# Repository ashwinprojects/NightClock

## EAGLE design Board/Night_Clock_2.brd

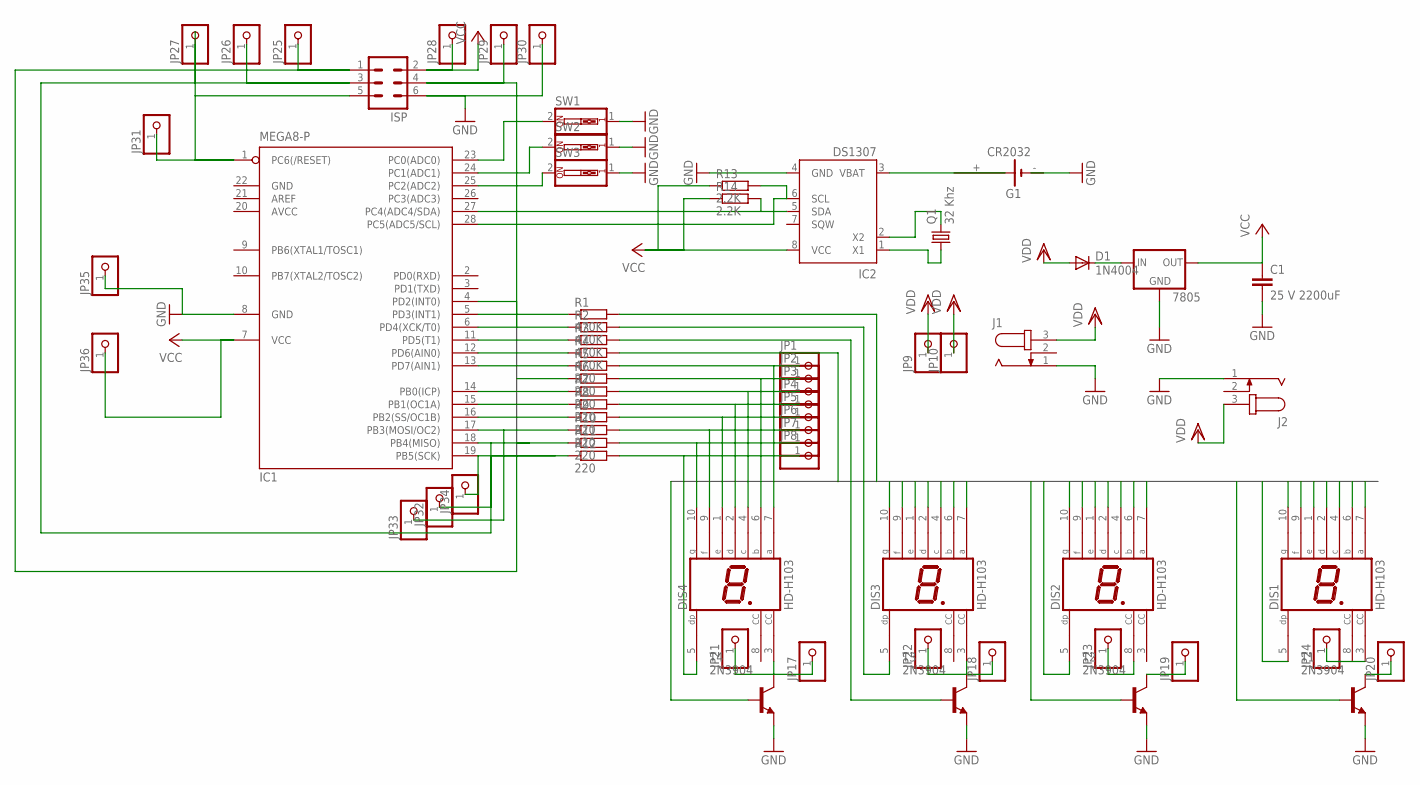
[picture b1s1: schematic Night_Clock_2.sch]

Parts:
7805: 78XXS
C1: 25 V 2200uF; C2.5-5
D1: 1N4004; DO41-10
DIS1, DIS2, DIS3, DIS4: HD-H103; HDSP-M
G1: CR2032; B2430UNI
IC1: MEGA8-P; DIL28-3
IC2: DS1307; DIP-8
ISP: MA03-2
J1, J2: JACK-PLUG1; SPC4078
JP1, JP2, JP3, JP4, JP5, JP6, JP7, JP8, JP9, JP10, JP17, JP18, JP19, JP20, JP21, JP22, JP23, JP24, JP25, JP26, JP27, JP28, JP29, JP30, JP31, JP32, JP33, JP34, JP35, JP36: PINHD-1X1; 1X01
Q1: 32 Khz; TC26V
R1, R2, R3, R4: 470K; 0207/10
R5, R6, R7, R8, R9, R10, R11, R12: 220; 0207/10
R13, R14: 2.2K; 0207/10
SW1, SW2, SW3: SW_DIP-1; EDG-01
T1, T2, T3, T4: 2N3904; TO92

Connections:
7SEG1: DIS1.7 (A), DIS2.4 (C), DIS3.7 (A), DIS4.9 (F), JP6.1, R10.2
7SEG2: DIS1.6 (B), DIS2.5 (DP), DIS3.6 (B), DIS4.10 (G), JP7.1, R11.2
7SEG3: DIS1.4 (C), DIS2.7 (A), DIS3.4 (C), DIS4.2 (D), JP3.1, R7.2
7SEG4: DIS1.2 (D), DIS2.9 (F), DIS3.2 (D), DIS4.4 (C), JP2.1, R6.2
7SEG5: DIS1.1 (E), DIS2.10 (G), DIS3.1 (E), DIS4.5 (DP), JP1.1, R5.2
7SEG6: DIS1.9 (F), DIS2.2 (D), DIS3.9 (F), DIS4.7 (A), JP5.1, R9.2
7SEG7: DIS1.10 (G), DIS2.1 (E), DIS3.10 (G), DIS4.6 (B), JP4.1, R8.2
7SEG8: DIS1.5 (DP), DIS2.6 (B), DIS3.5 (DP), DIS4.1 (E), JP8.1, R12.2
7SEG9: R4.2, T4.2 (B)
7SEG10: R3.2, T3.2 (B)
7SEG11: R2.2, T2.2 (B)
7SEG12: R1.2, T1.2 (B)
AVCC: IC1.20 (AVCC)
GND: 7805.GND, C1.2, G1.-@1 (-), IC1.8 (GND), IC1.22 (GND), IC2.4 (GND), ISP.6, J1.1, J2.1, JP30.1, JP35.1, SW1.1, SW2.1, SW3.1, T1.3 (E), T2.3 (E), T3.3 (E), T4.3 (E)
MEG2LED1: IC1.4 (PD2(INT0)), R1.1
MEG2LED2: IC1.5 (PD3(INT1)), R2.1
MEG2LED3: IC1.6 (PD4(XCK/T0)), R3.1
MEG2LED4: IC1.11 (PD5(T1)), R4.1
MEG2LED5: IC1.12 (PD6(AIN0)), R5.1
MEG2LED6: IC1.13 (PD7(AIN1)), R6.1
MEG2LED7: IC1.14 (PB0(ICP)), R7.1
MEG2LED8: IC1.15 (PB1(OC1A)), R8.1
MEG2LED9: IC1.16 (PB2(SS/OC1B)), R9.1
MEG2LED10: IC1.17 (PB3(MOSI/OC2)), ISP.4, JP29.1, JP33.1, R10.1
MEG2LED11: IC1.18 (PB4(MISO)), ISP.1, JP25.1, JP32.1, R11.1
MEG2LED12: IC1.19 (PB5(SCK)), ISP.3, JP26.1, JP34.1, R12.1
unnamed: IC1.1 (PC6(/RESET)), ISP.5, JP27.1, JP31.1
unnamed: IC1.27 (PC4(ADC4/SDA)), IC2.5 (SDA), R14.2
unnamed: IC1.28 (PC5(ADC5/SCL)), IC2.6 (SCL), R13.2
unnamed: JP17.1, T4.1 (C)
unnamed: JP18.1, T3.1 (C)
unnamed: IC1.23 (PC0(ADC0)), SW1.2
unnamed: IC1.24 (PC1(ADC1)), SW2.2
unnamed: IC1.25 (PC2(ADC2)), SW3.2
unnamed: G1.+@4 (+), IC2.3 (VBAT)
unnamed: IC2.2 (X2), Q1.2
unnamed: IC2.1 (X1), Q1.1
unnamed: 7805.IN, D1.C
unnamed: JP19.1, T2.1 (C)
unnamed: JP20.1, T1.1 (C)
unnamed: DIS1.3 (CC), JP24.1
unnamed: DIS2.8 (CC), JP23.1
unnamed: DIS3.3 (CC), JP22.1
unnamed: DIS4.3 (CC), JP21.1
VCC: 7805.OUT, C1.1, IC1.7 (VCC), IC2.8 (VCC), ISP.2, JP28.1, JP36.1, R13.1, R14.1
VDD: D1.A, J1.3, J2.3, JP9.1, JP10.1

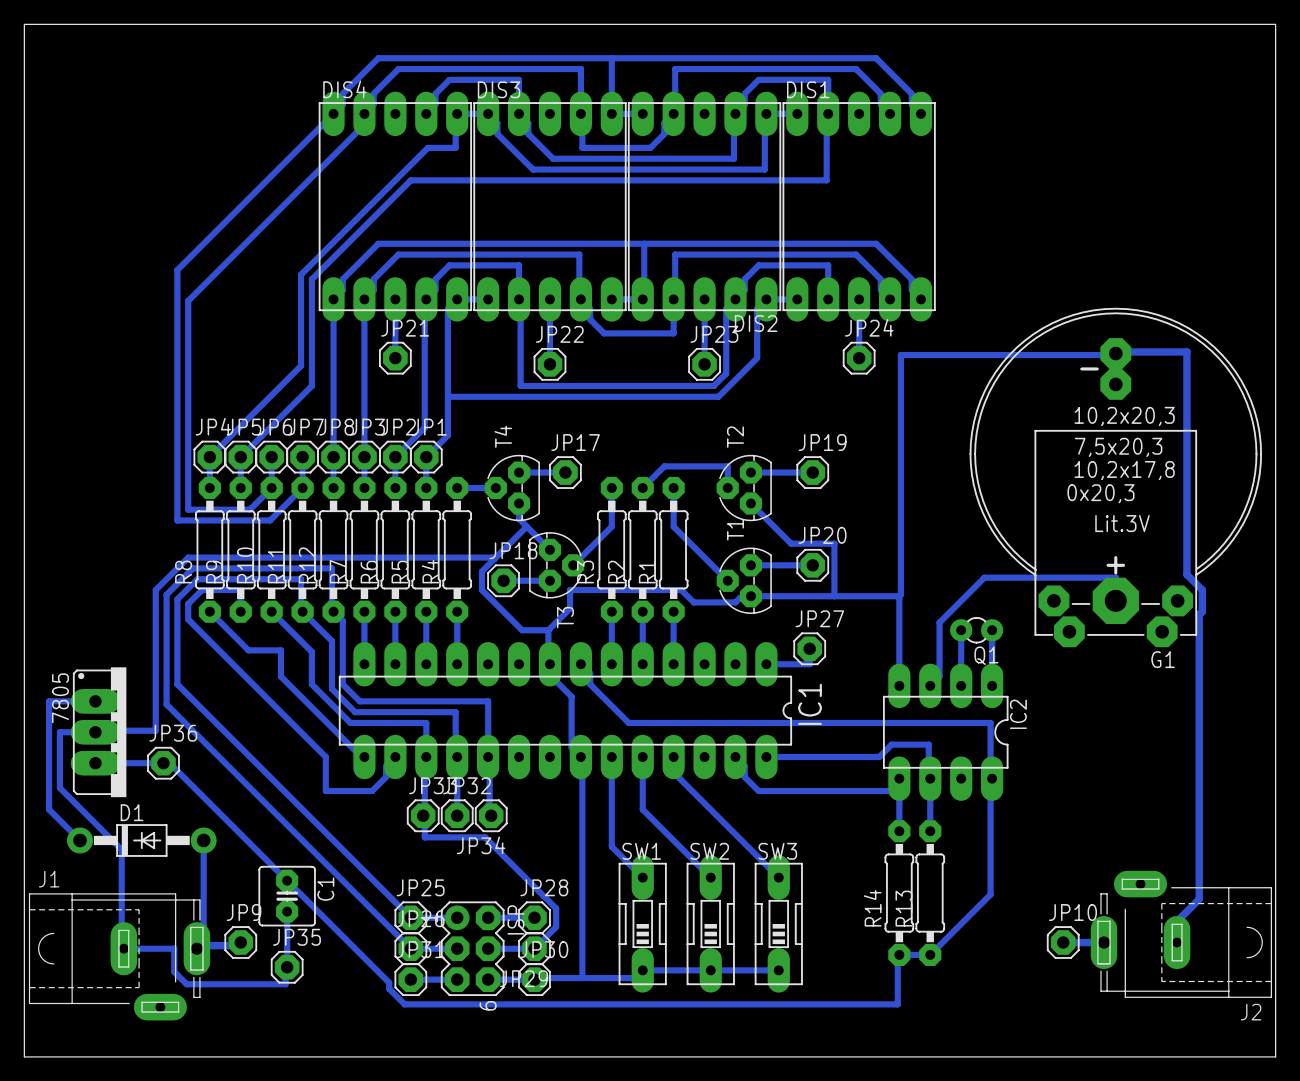
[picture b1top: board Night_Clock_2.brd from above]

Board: 2 copper layers, 102.8 x 84.8 mm, 65 parts (0 on the bottom side), 45 nets.

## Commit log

2014-01-11 Night Clock
    Open Source Night Clock
2014-01-11 Night Clock
2014-01-26 Gave components values
2014-01-26 Adding some board details
2014-01-26 Adding License
2014-01-28 Create gh-pages branch via GitHub
